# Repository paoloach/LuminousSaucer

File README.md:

# Luminous Saucer

The indoor light is very minor to the sun, especially in the summer.

The aim of this project is to allow those plants needing to receive a grea quantity of light to be illuminated properly.

It consists in a saucer containing the all the ESP32 and the electronic but the lights and on the top the lights. The idea is to put a vase on the saucer and allow the plant to receive all the light it needs.

The light can be controlled by homeassistant or by the android application included in the project. You can set the light period and the maximum light. 

The project contains a 3d STL file for allow you to print the saucer and the light holder, a schematic and a gaber file for printing the electronic PCB, the configuration file for programming the ESP32 by esphome and the source of the android application

something like

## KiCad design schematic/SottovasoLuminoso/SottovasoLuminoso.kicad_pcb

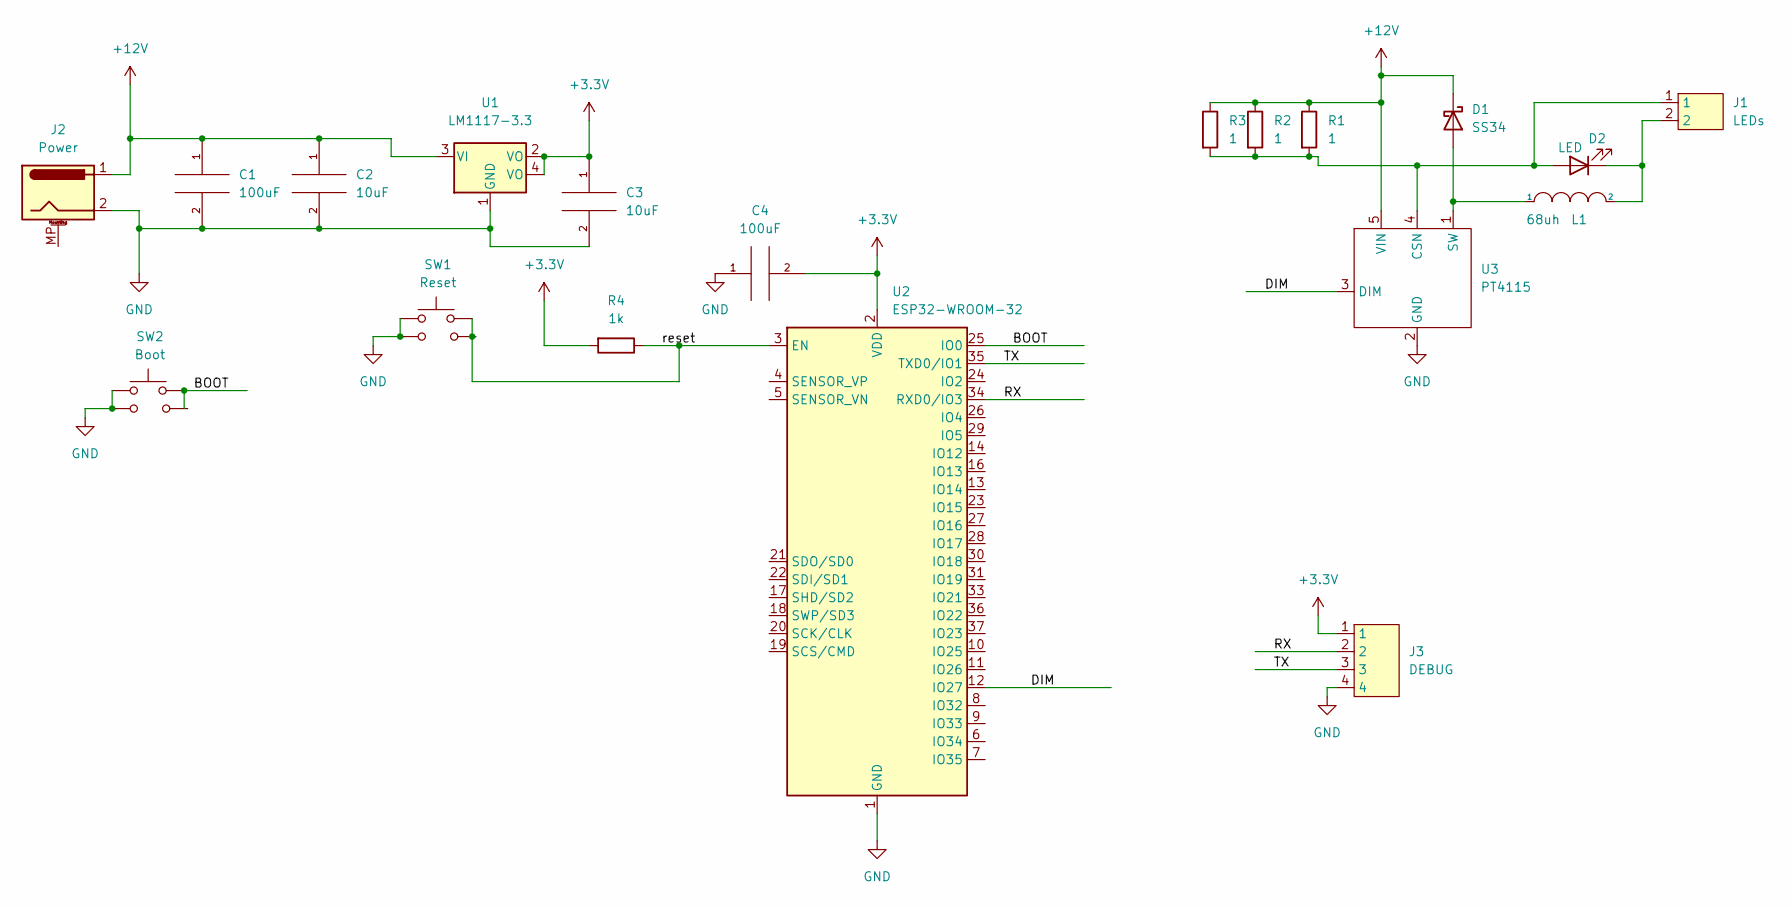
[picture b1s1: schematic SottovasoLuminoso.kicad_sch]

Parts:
C1: 100uF; C_1210_3225Metric_Pad1.33x2.70mm_HandSolder
C2, C3: 10uF; C_0603_1608Metric_Pad1.08x0.95mm_HandSolder
C4: 100uF; C_0603_1608Metric_Pad1.08x0.95mm_HandSolder
D1: SS34
D2: LED
J1: LEDs; XH2-H
J2: Power; PinHeader_1x02_P2.54mm_Vertical
J3: DEBUG; XH4-V
L1: 68uh; RH127
R1, R2, R3: 1; R_0805_2012Metric_Pad1.20x1.40mm_HandSolder
R4: 1k; R_0603_1608Metric_Pad0.98x0.95mm_HandSolder
SW1: Reset; ButtonSMD
SW2: Boot; ButtonSMD
U1: LM1117-3.3; SOT-223
U2: ESP32-WROOM-32
U3: PT4115; SOT-89-5_Handsoldering

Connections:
+3V3: C3.1, C4.2, J3.1, R4.2, U1.2 (VO), U1.4 (VO), U2.2 (VDD)
+12V: C1.1, C2.1, D1.1 (K), J2.1, R1.1, R2.1, R3.1, U1.3 (VI), U3.5 (VIN)
/BOOT: SW2.2, U2.25 (IO0)
/DIM: U2.12 (IO27), U3.3 (DIM)
/RX: J3.2, U2.34 (RXD0/IO3)
/TX: J3.3, U2.35 (TXD0/IO1)
/reset: R4.1, SW1.2, SW1.4 (2), U2.3 (EN)
GND: C1.2, C2.2, C3.2, C4.1, J2.2, J3.4, SW1.1, SW1.3 (1), SW2.1, SW2.3 (1), U1.1 (GND), U2.1 (GND), U2.15 (GND), U2.38 (GND), U2.39 (GND), U3.2 (GND)
unnamed: D2.1 (K), J1.2, L1.2
unnamed: D1.2 (A), L1.1, U3.1 (SW)
unnamed: D2.2 (A), J1.1, R1.2, R2.2, R3.2, U3.4 (CSN)

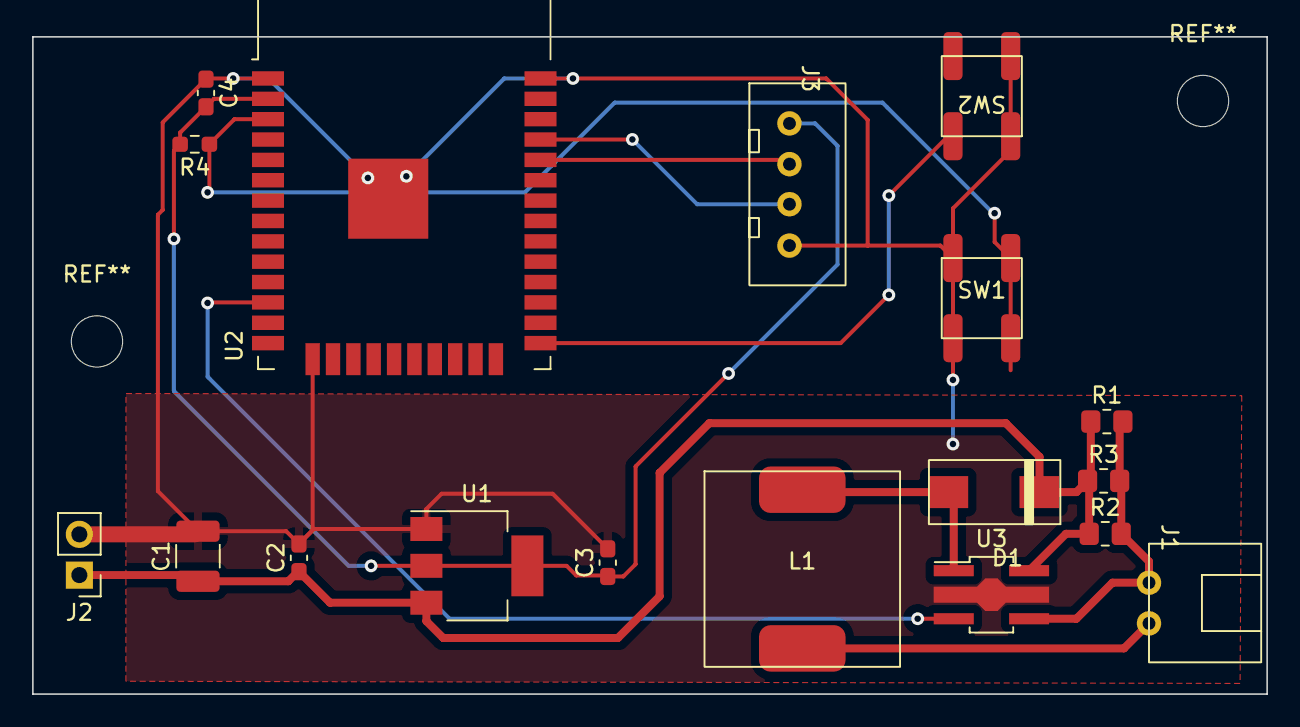
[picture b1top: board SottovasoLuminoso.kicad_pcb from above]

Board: 2 copper layers, 77.0 x 41.0 mm, 18 parts (0 on the bottom side), 11 nets.

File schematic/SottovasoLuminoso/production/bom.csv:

Designator,Footprint,Quantity,Value,LCSC Part #
C1,C_1210_3225Metric_Pad1.33x2.70mm_HandSolder,1,100uF,
"C2, C3",C_0603_1608Metric_Pad1.08x0.95mm_HandSolder,2,10uF,
C4,C_0603_1608Metric_Pad1.08x0.95mm_HandSolder,1,100uF,
D1,SS34,1,SS34,
J1,XH2-H,1,LEDs,
J2,PinHeader_1x02_P2.54mm_Vertical,1,Power,
J3,XH4-V,1,DEBUG,
L1,RH127,1,68uh,
"R1, R2, R3",R_0805_2012Metric_Pad1.20x1.40mm_HandSolder,3,1,
R4,R_0603_1608Metric_Pad0.98x0.95mm_HandSolder,1,1k,
SW1,ButtonSMD,1,Reset,
SW2,ButtonSMD,1,Boot,
U1,SOT-223,1,LM1117-3.3,
U2,ESP32-WROOM-32,1,ESP32-WROOM-32,
U3,SOT-89-5_Handsoldering,1,PT4115,

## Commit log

2022-12-28 some changes
2022-12-30 Add Protobuf communication with App
2022-12-31 Better layout
2022-12-31 protobuffer classes
2023-01-01 Android App
2023-01-01 Android App-reconnect to disconnected devices
2023-01-02 Android App-change icon
2023-01-03 Some minor fixes
2023-01-03 Add first version of README
2023-01-03 merge
2023-01-03 Add image in the README
2023-01-04 update esphome file
2023-01-05 Update esphome
